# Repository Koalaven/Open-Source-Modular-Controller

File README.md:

# Open Source Modular Controller

Using a modular, reconfigurable hardware architecture to create a customizable USB HID game controller.

## Project Details

The Open Source Modular Controller project is a fully modular and customizable gaming input system. Users can freely rearrange joysticks, buttons, and future input modules on a set of interchangeable receiver boards to build a layout that fits their gameplay style, ergonomic needs, or accessibility requirements.

The controller connects over USB and is recognized as a standard Human Interface Device (HID) with no additional drivers required.

## Current State

The current prototype includes:
- A functional ESP32‑S3‑based main controller
- Hot-swappable joystick and button modules
- Receiver boards that can be placed anywhere in the 3D‑printed shell
- USB HID communication via TinyUSB

The system operates as a recognized USB gamepad on Windows. Some hardware issues were identified and corrected in updated revisions.

## Project Structure

The repository is organized as follows:
1. **Firmware** – ESP32‑S3 code handling HID communication and module input processing.  
   *Link: [Firmware](/Controller%20Code/Firmware.md)*
2. **Software** – PC‑side utilities or test scripts (coming soon).  
3. **Hardware** – KiCad project files, schematics, PCBs, and 3D‑printed shell models.  
   *Link: [Hardware](/Hardware/Hardware.md)*
4. **Documentation** – Assembly instructions, diagrams, semester report, and testing notes.  
   *Link: [Documentation](/Documents/Documents.md)*

## Features

- Modular input modules (buttons, joystick, future sensors)
- Repositionable input layout using multiple receiver boards
- ESP32‑S3 native USB HID support
- Open‑source hardware and firmware
- Premade 3D‑printable ergonomic controller shell

## System Architecture

Core system components include:
- **Receiver boards** distributing power, signals, and micro-controller
- **Module boards** for inputs (joystick/button)
- **3D‑printed enclosure** with heat‑set inserts for secure mounting

USB HID enumeration and report handling are implemented using TinyUSB. Modules communicate through standardized connectors to the controller board.

## Bill of Materials
A full BOM including the ESP32‑S3 boards, connector sets, resistors, capacitors, PCBs, wire, and 3D‑printed components is provided in the documentation.  
*[BOM](/Documents/BOM.md)*

## Tools Used
### Software
- Arduino IDE
- KiCad
- Fusion (frame design)
- GitHub Desktop
- Cura slicer

### Hardware
- 3D printer
- Soldering iron
- Hot air station
- Multimeter
- Tweezers

## Assembly Overview
1. Gather materials (refer to BOM).  
2. Order PCBs (Gerber files included).  
3. 3D print shell and module housings.  
4. Clean and prepare boards.  
5. Solder components (headers, ESP32 module, connectors, buttons/joysticks).  
6. Upload firmware via Arduino IDE.  
7. Install modules into the shell.  
8. Test controller.  

[Full assembly guide](/Documents/Assembly%20guide.md)

## What the Project Could Use Next
1. On‑board processing for more advanced input mapping
2. PCB adjustment and testing
3. Wireless mode using Bluetooth HID
4. Additional module types (battery, gyroscope, sliders, touchpads)

## Semester End Report
For the Enterprise Program at Michigan Tech there is a end of semester report for the project to summarize the progress of the project. [Link](/Documents/Open%20Source%20Modular%20Controller%20Fall%202025%20Final%20Report.pdf)

## Acknowledgements
This project is supported by the Open Source Hardware Enterprise at Michigan Technological University.

## Helpful Links
- [TinyUSB](https://docs.tinyusb.org/en/latest/)
- [Gamepad tester](https://hardwaretester.com/gamepad)

## References

[GitHub Doc](https://docs.github.com/en/get-started/writing-on-github/getting-started-with-writing-and-formatting-on-github/basic-writing-and-formatting-syntax#links)

[Alpakka conroller](https://inputlabs.io/alpakka)

[Proteus ControllerTM kit](https://byowave.com/products/proteus-controller )

[Thrustmaster](https://eshop.thrustmaster.com/en_us/gamepads/pc.html)

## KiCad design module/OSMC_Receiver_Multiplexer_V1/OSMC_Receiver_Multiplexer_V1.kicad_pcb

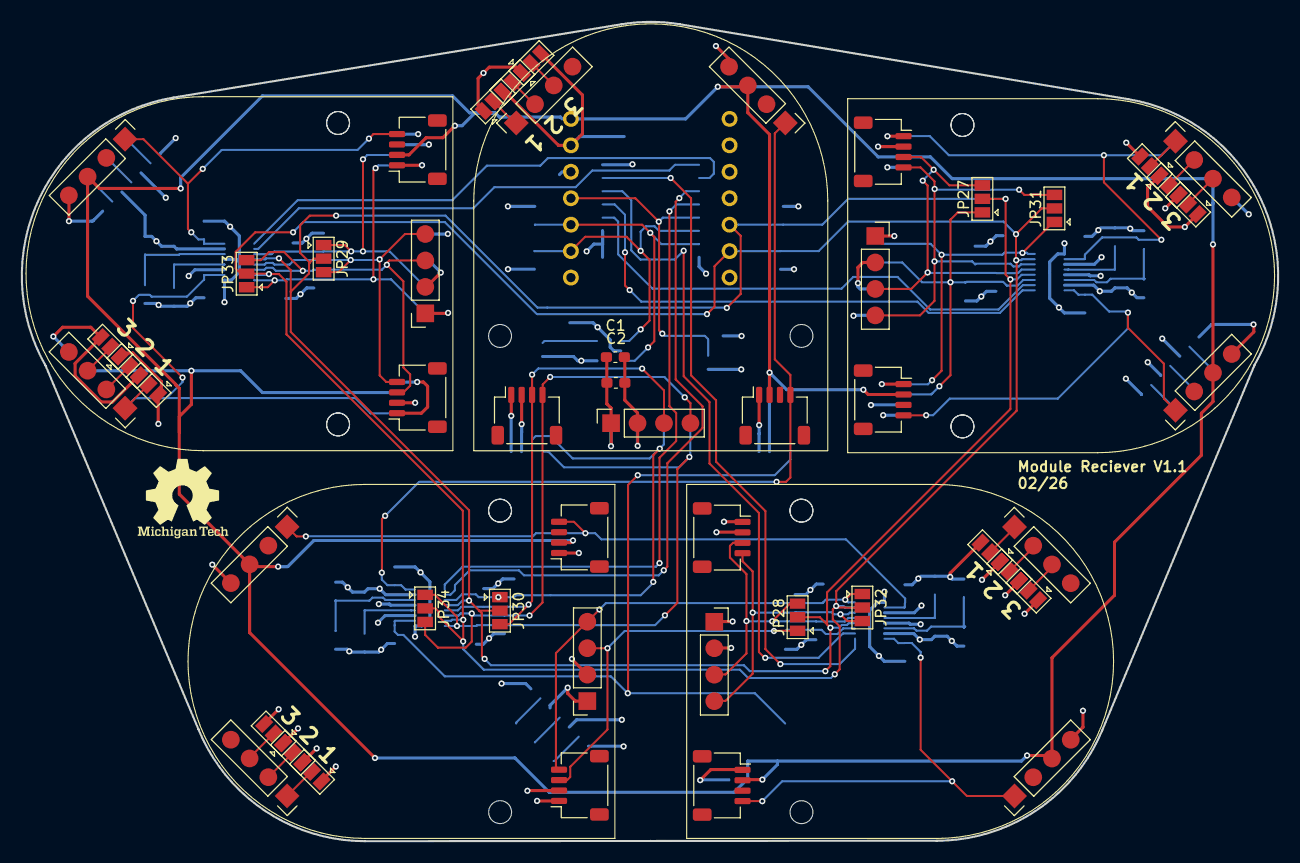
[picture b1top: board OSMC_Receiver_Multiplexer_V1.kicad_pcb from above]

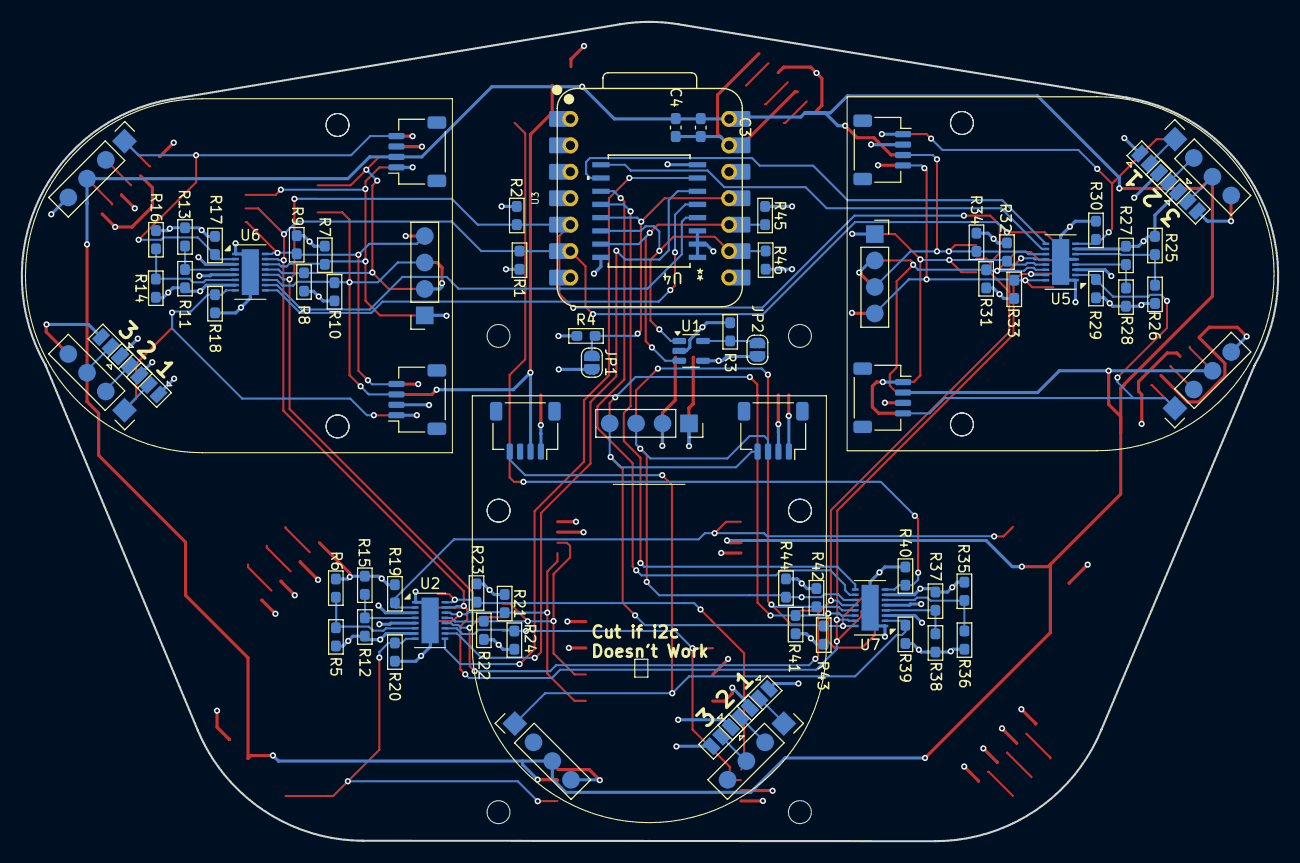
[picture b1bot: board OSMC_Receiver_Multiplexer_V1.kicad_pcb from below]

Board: 4 copper layers, 120.7 x 78.7 mm, 99 parts (69 on the bottom side), 73 nets.

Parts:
C1, C2: .1 u; C_0603_1608Metric_Pad1.08x0.95mm_HandSolder
C3, C4: C; C_0603_1608Metric_Pad1.08x0.95mm_HandSolder
JP1: int; SolderJumper-2_P1.3mm_Open_RoundedPad1.0x1.5mm
JP2: WP; SolderJumper-2_P1.3mm_Open_RoundedPad1.0x1.5mm
JP3, JP4, JP5, JP6, JP7, JP8, JP9, JP10, JP11, JP12, JP13, JP14, JP15, JP16, JP17, JP18, JP19, JP20, JP21, JP22, JP23, JP24, JP25, JP26, JP27, JP28, JP29, JP30, JP31, JP32, JP33, JP34: SolderJumper_3_Open; SolderJumper-3_P1.3mm_Open_Pad1.0x1.5mm
R1, R2, R7, R8, R9, R10, R17, R18, R19, R20, R21, R22, R23, R24, R29, R30, R31, R32, R33, R34, R39, R40, R41, R42, R43, R44, R45, R46: 10k; R_0603_1608Metric_Pad1.05x0.95mm_HandSolder
R3, R4: 100k; R_0603_1608Metric_Pad1.05x0.95mm_HandSolder
R5, R11: 976k; R_0603_1608Metric_Pad1.05x0.95mm_HandSolder
R6: 182k; R_0603_1608Metric_Pad1.05x0.95mm_HandSolder
R12: 1M; R_0603_1608Metric_Pad1.05x0.95mm_HandSolder
R13: 102k; R_0603_1608Metric_Pad1.05x0.95mm_HandSolder
R14: R; R_0603_1608Metric_Pad1.05x0.95mm_HandSolder
R15: 280k; R_0603_1608Metric_Pad1.05x0.95mm_HandSolder
R16: 0; R_0603_1608Metric_Pad1.05x0.95mm_HandSolder
R25, R27, R35, R37: 1000k; R_0603_1608Metric_Pad1.05x0.95mm_HandSolder
R26: 392k; R_0603_1608Metric_Pad1.05x0.95mm_HandSolder
R28: 523k; R_0603_1608Metric_Pad1.05x0.95mm_HandSolder
R36: 681k; R_0603_1608Metric_Pad1.05x0.95mm_HandSolder
R38: 887k; R_0603_1608Metric_Pad1.05x0.95mm_HandSolder
U1: 24AA02-OT; SOT-23-5
U2, U5, U6, U7: LTC4317; DFN-16-1EP_3x5mm_P0.5mm_EP1.66x4.4mm
U3: XIAO-ESP32-S3-DIP
U4: PCF8574DWR; DW16-L
U13, U14, U15, U16, U17, U18, U19, U20: OSMC Module Board; Module standard pin large outline

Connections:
+5V: C3.1, C4.1, U3.14 (5V), U13.10 (5V), U13.15 (5V), U14.10 (5V), U14.15 (5V), U15.10 (5V), U15.15 (5V), U16.10 (5V), U16.15 (5V), U17.10 (5V), U17.15 (5V), U18.10 (5V), U18.15 (5V), U19.10 (5V), U19.15 (5V), U20.10 (5V), U20.15 (5V)
/INT: JP1.1 (A), R4.2, U3.11 (PA6_A10_D10_MOSI), U4.13 (~INT)
/Modules/EN0: R18.2, U6.8 (ENABLE1), U13.12 (Det), U13.13 (Det)
/Modules/EN1: R17.2, U6.2 (ENABLE2), U15.12 (Det), U15.13 (Det)
/Modules/EN2: R20.2, U2.8 (ENABLE1), U16.12 (Det), U16.13 (Det)
/Modules/EN3: R19.2, U2.2 (ENABLE2), U18.12 (Det), U18.13 (Det)
/Modules/EN4: R30.2, U5.8 (ENABLE1), U17.12 (Det), U17.13 (Det)
/Modules/EN5: R29.2, U5.2 (ENABLE2), U20.12 (Det), U20.13 (Det)
/Modules/EN6: R40.2, U7.8 (ENABLE1), U14.12 (Det), U14.13 (Det)
/Modules/EN7: R39.2, U7.2 (ENABLE2), U19.12 (Det), U19.13 (Det)
/Modules/P0: U4.4 (P0), U6.10 (READY1)
/Modules/P1: U4.5 (P1), U6.9 (READY2)
/Modules/P2: U2.10 (READY1), U4.6 (P2)
/Modules/P3: U2.9 (READY2), U4.7 (P3)
/Modules/P4: U4.9 (P4), U5.10 (READY1)
/Modules/P5: U4.10 (P5), U5.9 (READY2)
/Modules/P6: U4.11 (P6), U7.10 (READY1)
/Modules/P7: U4.12 (P7), U7.9 (READY2)
/Modules/SCL0: JP31.3 (B), R7.2, U6.14 (SCLOUT1), U13.4 (SCL), U13.8 (SCL)
/Modules/SCL1: JP31.1 (A), R9.2, U6.16 (SCLOUT2), U15.4 (SCL), U15.8 (SCL)
/Modules/SCL2: JP32.3 (B), R21.2, U2.14 (SCLOUT1), U16.4 (SCL), U16.8 (SCL)
/Modules/SCL3: JP32.1 (A), R23.2, U2.16 (SCLOUT2), U18.4 (SCL), U18.8 (SCL)
/Modules/SCL4: JP33.3 (B), R31.2, U5.14 (SCLOUT1), U17.3 (SDA), U17.7 (SDA)
/Modules/SCL5: JP33.1 (A), R33.2, U5.16 (SCLOUT2), U20.4 (SCL), U20.8 (SCL)
/Modules/SCL6: JP34.3 (B), R41.2, U7.14 (SCLOUT1), U14.4 (SCL), U14.8 (SCL)
/Modules/SCL7: JP34.1 (A), R43.2, U7.16 (SCLOUT2), U19.4 (SCL), U19.8 (SCL)
/Modules/SDA0: JP27.3 (B), R8.2, U6.13 (SDAOUT1), U13.3 (SDA), U13.7 (SDA)
/Modules/SDA1: JP27.1 (A), R10.2, U6.11 (SDAOUT2), U15.3 (SDA), U15.7 (SDA)
/Modules/SDA2: JP28.3 (B), R22.2, U2.13 (SDAOUT1), U16.3 (SDA), U16.7 (SDA)
/Modules/SDA3: JP28.1 (A), R24.2, U2.11 (SDAOUT2), U18.3 (SDA), U18.7 (SDA)
/Modules/SDA4: JP29.3 (B), R32.2, U5.13 (SDAOUT1), U17.4 (SCL), U17.8 (SCL)
/Modules/SDA5: JP29.1 (A), R34.2, U5.11 (SDAOUT2), U20.3 (SDA), U20.7 (SDA)
/Modules/SDA6: JP30.3 (B), R42.2, U7.13 (SDAOUT1), U14.3 (SDA), U14.7 (SDA)
/Modules/SDA7: JP30.1 (A), R44.2, U7.11 (SDAOUT2), U19.3 (SDA), U19.7 (SDA)
/SCL: JP31.2 (C), JP32.2 (C), JP33.2 (C), JP34.2 (C), R1.2, U2.15 (SCLIN), U3.6 (PA9_A5_D5_SCL), U5.15 (SCLIN), U6.15 (SCLIN), U7.15 (SCLIN)
/SCL1: R46.2, U1.1 (SCL), U3.9 (PA7_A8_D8_SCK), U4.14 (SCL)
/SDA: JP27.2 (C), JP28.2 (C), JP29.2 (C), JP30.2 (C), R2.2, U2.12 (SDAIN), U3.5 (PA8_A4_D4_SDA), U5.12 (SDAIN), U6.12 (SDAIN), U7.12 (SDAIN)
/SDA1: R45.2, U1.3 (SDA), U3.10 (PA5_A9_D9_MISO), U4.15 (SDA)
/wp: JP2.1 (A), R3.2, U1.5 (WP)
GND: C1.2, C2.2, C3.2, C4.2, JP3.3 (B), JP4.3 (B), JP5.3 (B), JP6.3 (B), JP7.3 (B), JP8.3 (B), JP9.3 (B), JP10.3 (B), JP11.3 (B), JP12.3 (B), JP13.3 (B), JP14.3 (B), JP15.3 (B), JP16.3 (B), JP17.3 (B), JP18.3 (B), JP19.3 (B), JP20.3 (B), JP21.3 (B), JP22.3 (B), JP23.3 (B), JP24.3 (B), JP25.3 (B), JP26.3 (B), R3.1, R4.1, R6.2, R13.2, R15.2, R16.2, R17.1, R18.1, R19.1, R20.1, R26.2, R28.2, R29.1, R30.1, R36.2, R38.2, R39.1, R40.1, U1.2 (V_{SS}), U2.1 (GND), U2.3 (XORH2), U2.5 (XORH1), U2.17 (EP), U3.13 (GND), U4.1 (A0), U4.2 (A1), U4.3 (A2), U4.8 (GND), U5.1 (GND), U5.3 (XORH2), U5.5 (XORH1), U5.17 (EP), U6.1 (GND), U6.3 (XORH2), U6.5 (XORH1), U6.17 (EP), U7.1 (GND), U7.3 (XORH2), U7.5 (XORH1), U7.17 (EP), U13.1 (Gnd), U13.5 (Gnd), U13.9 (Gnd), U13.16 (GND), U14.1 (Gnd), U14.5 (Gnd), U14.9 (Gnd), U14.16 (GND), U15.1 (Gnd), U15.5 (Gnd), U15.9 (Gnd), U15.16 (GND), U16.1 (Gnd), U16.5 (Gnd), U16.9 (Gnd), U16.16 (GND), U17.1 (Gnd), U17.5 (Gnd), U17.9 (Gnd), U17.16 (GND), U18.1 (Gnd), U18.5 (Gnd), U18.9 (Gnd), U18.16 (GND), U19.1 (Gnd), U19.5 (Gnd), U19.9 (Gnd), U19.16 (GND), U20.1 (Gnd), U20.5 (Gnd), U20.9 (Gnd), U20.16 (GND)
unnamed: JP3.2 (C), U16.18 (A3)
unnamed: JP4.2 (C), U16.19 (A2)
unnamed: JP5.2 (C), U16.20 (A1)
unnamed: JP6.2 (C), U15.18 (A3)
unnamed: JP7.2 (C), U15.19 (A2)
unnamed: JP8.2 (C), U15.20 (A1)
unnamed: JP9.2 (C), U13.18 (A3)
unnamed: JP10.2 (C), U13.19 (A2)
unnamed: JP11.2 (C), U13.20 (A1)
unnamed: JP12.2 (C), U18.18 (A3)
unnamed: JP13.2 (C), U18.19 (A2)
unnamed: JP14.2 (C), U18.20 (A1)
unnamed: JP15.2 (C), U19.18 (A3)
unnamed: JP16.2 (C), U19.19 (A2)
unnamed: JP17.2 (C), U19.20 (A1)
unnamed: JP18.2 (C), U17.18 (A3)
unnamed: JP19.2 (C), U17.19 (A2)
unnamed: JP20.2 (C), U17.20 (A1)
unnamed: JP21.2 (C), U20.18 (A3)
unnamed: JP22.2 (C), U20.19 (A2)
unnamed: JP23.2 (C), U20.20 (A1)
unnamed: JP24.2 (C), U14.18 (A3)
unnamed: JP25.2 (C), U14.19 (A2)
unnamed: JP26.2 (C), U14.20 (A1)
unnamed: R5.2, R6.1, U2.6 (XORL1)
unnamed: R12.2, R15.1, U2.4 (XORL2)
unnamed: R25.2, R26.1, U5.6 (XORL1)
unnamed: R27.2, R28.1, U5.4 (XORL2)
unnamed: R14.2, R16.1, U6.6 (XORL1)
unnamed: R11.2, R13.1, U6.4 (XORL2)
unnamed: R35.2, R36.1, U7.6 (XORL1)
unnamed: R37.2, R38.1, U7.4 (XORL2)
VDD: C1.1, C2.1, JP1.2 (B), JP2.2 (B), JP3.1 (A), JP4.1 (A), JP5.1 (A), JP6.1 (A), JP7.1 (A), JP8.1 (A), JP9.1 (A), JP10.1 (A), JP11.1 (A), JP12.1 (A), JP13.1 (A), JP14.1 (A), JP15.1 (A), JP16.1 (A), JP17.1 (A), JP18.1 (A), JP19.1 (A), JP20.1 (A), JP21.1 (A), JP22.1 (A), JP23.1 (A), JP24.1 (A), JP25.1 (A), JP26.1 (A), R1.1, R2.1, R5.1, R7.1, R8.1, R9.1, R10.1, R11.1, R12.1, R14.1, R21.1, R22.1, R23.1, R24.1, R25.1, R27.1, R31.1, R32.1, R33.1, R34.1, R35.1, R37.1, R41.1, R42.1, R43.1, R44.1, R45.1, R46.1, U1.4 (V_{CC}), U2.7 (VCC), U3.12 (3V3), U4.16 (VDD), U5.7 (VCC), U6.7 (VCC), U7.7 (VCC), U13.2 (Vdd), U13.6 (Vdd), U14.2 (Vdd), U14.6 (Vdd), U15.2 (Vdd), U15.6 (Vdd), U16.2 (Vdd), U16.6 (Vdd), U17.2 (Vdd), U17.6 (Vdd), U18.2 (Vdd), U18.6 (Vdd), U19.2 (Vdd), U19.6 (Vdd), U20.2 (Vdd), U20.6 (Vdd)

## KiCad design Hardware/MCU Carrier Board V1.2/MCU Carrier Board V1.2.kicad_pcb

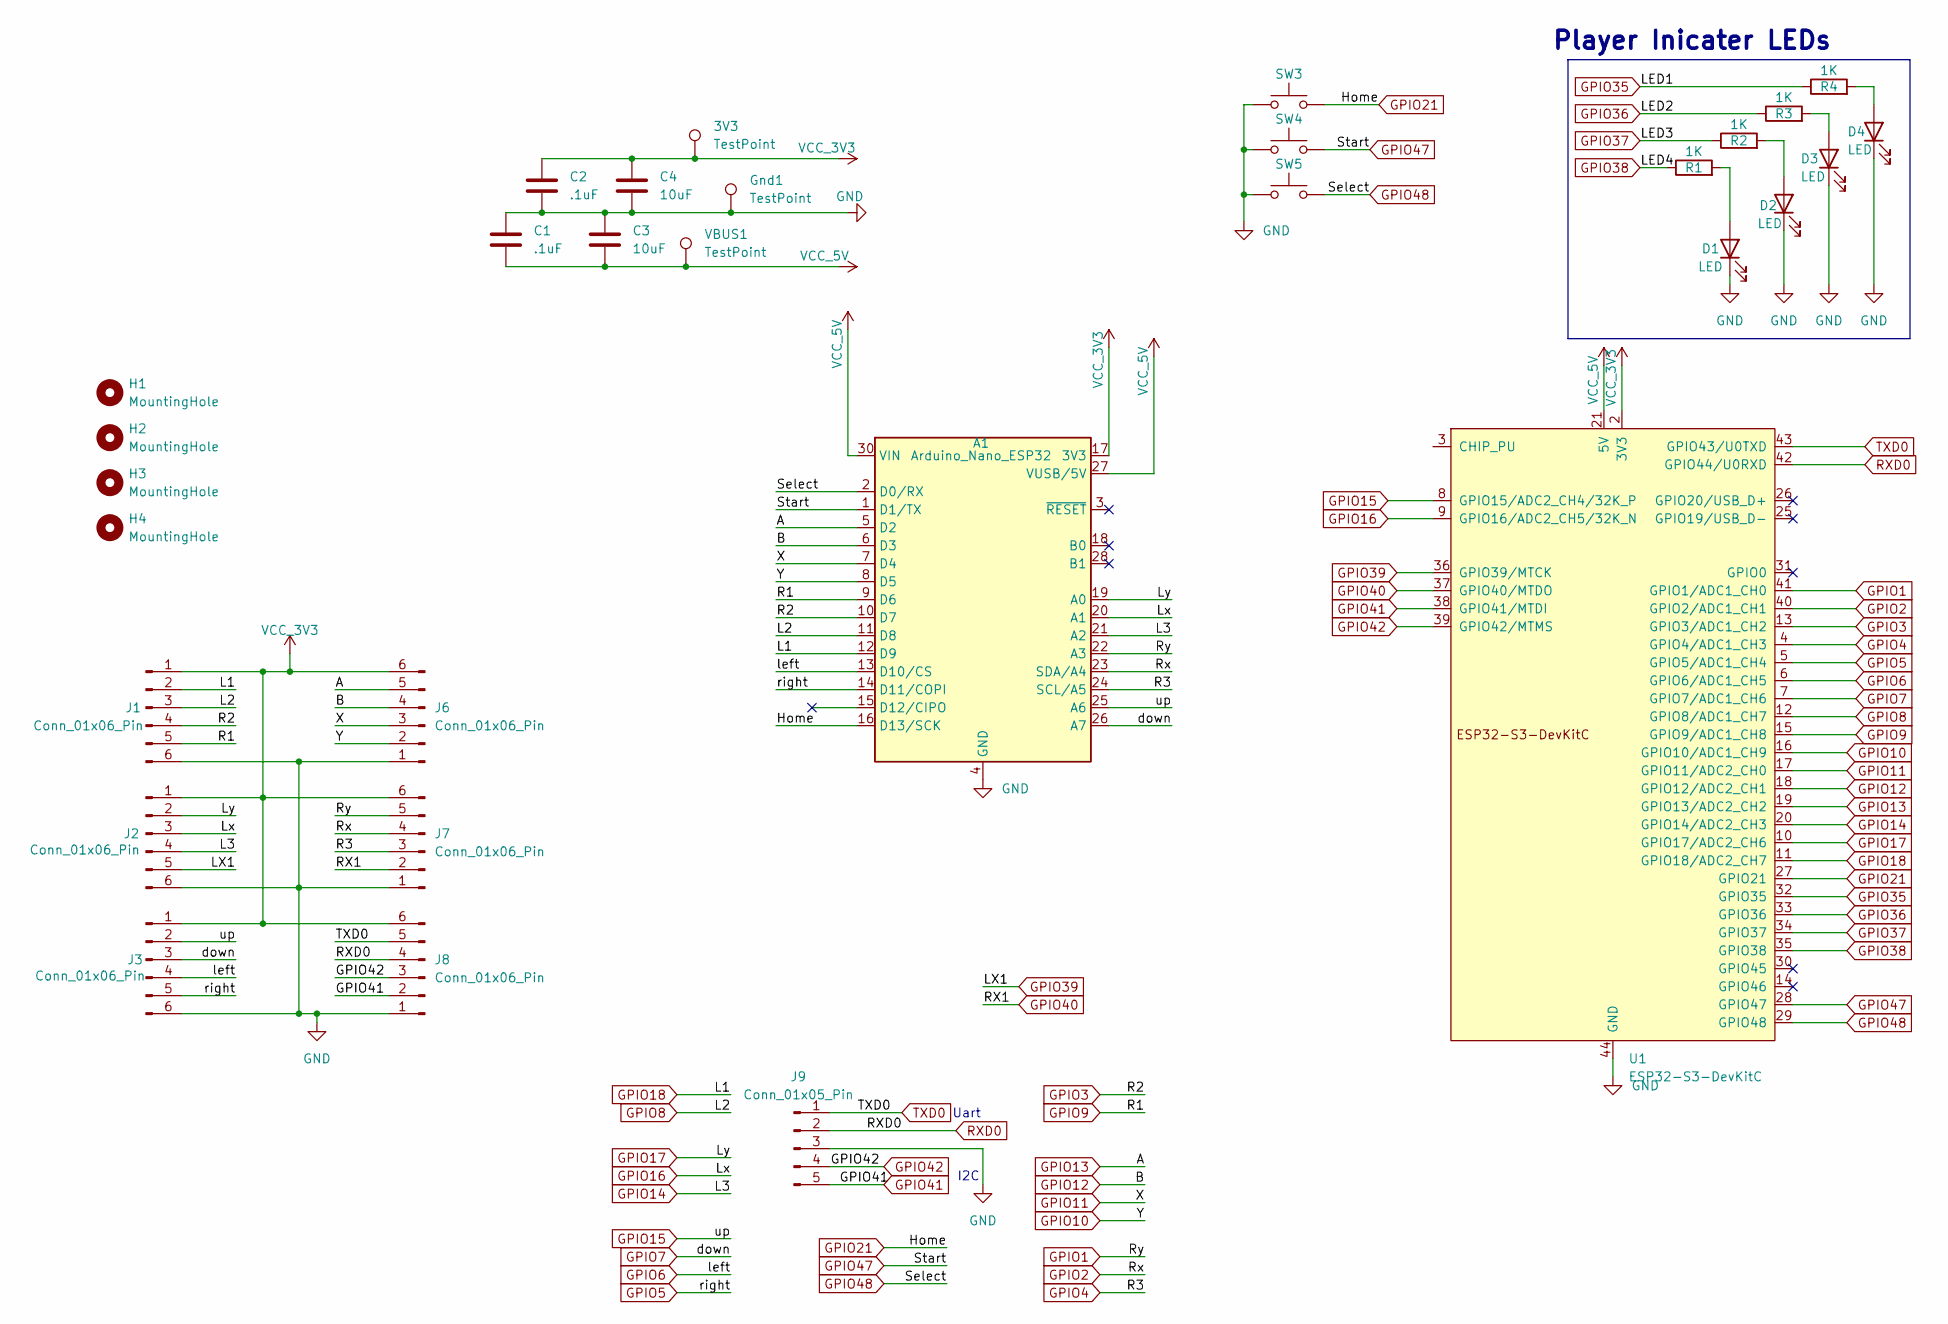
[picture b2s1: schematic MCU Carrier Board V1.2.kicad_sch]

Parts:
3V3: TestPoint; TestPoint_Pad_D1.0mm
A1: Arduino_Nano_ESP32; Arduino_Nano_WithMountingHoles
C1, C2: .1uF; C_0603_1608Metric_Pad1.08x0.95mm_HandSolder
C3, C4: 10uF; C_0603_1608Metric_Pad1.08x0.95mm_HandSolder
D1, D2, D3, D4: LED; LED_0603_1608Metric_Pad1.05x0.95mm_HandSolder
Gnd1: TestPoint; TestPoint_Pad_D1.0mm
H1, H2, H3, H4: MountingHole; MountingHole_2.5mm
J1, J2, J3, J6, J7, J8: Conn_01x06_Pin; PinHeader_1x06_P2.54mm_Vertical
J9: Conn_01x05_Pin; JST_EH_S5B-EH_1x05_P2.50mm_Horizontal
R1, R2, R3, R4: 1K; R_0603_1608Metric_Pad0.98x0.95mm_HandSolder
SW3, SW4, SW5: SW_Push; SW_Push_1P1T_XKB_TS-1187A
U1: ESP32-S3-DevKitC
VBUS1: TestPoint; TestPoint_Pad_D1.0mm

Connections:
GND: A1.4 (GND), A1.29 (GND), C1.1, C2.2, C3.1, C4.2, D1.1 (K), D2.1 (K), D3.1 (K), D4.1 (K), Gnd1.1, J1.6, J2.6, J3.6, J6.1, J7.1, J8.1, J9.3, SW3.1, SW4.1, SW5.1, U1.22 (GND), U1.23 (GND), U1.24 (GND), U1.44 (GND)
GPIO1: A1.22 (A3), J7.5, U1.41 (GPIO1/ADC1_CH0)
GPIO2: A1.23 (SDA/A4), J7.4, U1.40 (GPIO2/ADC1_CH1)
GPIO3: A1.10 (D7), J1.4, U1.13 (GPIO3/ADC1_CH2)
GPIO4: A1.24 (SCL/A5), J7.3, U1.4 (GPIO4/ADC1_CH3)
GPIO5: A1.14 (D11/COPI), J3.5, U1.5 (GPIO5/ADC1_CH4)
GPIO6: A1.13 (D10/CS), J3.4, U1.6 (GPIO6/ADC1_CH5)
GPIO7: A1.26 (A7), J3.3, U1.7 (GPIO7/ADC1_CH6)
GPIO8: A1.11 (D8), J1.3, U1.12 (GPIO8/ADC1_CH7)
GPIO9: A1.9 (D6), J1.5, U1.15 (GPIO9/ADC1_CH8)
GPIO10: A1.8 (D5), J6.2, U1.16 (GPIO10/ADC1_CH9)
GPIO11: A1.7 (D4), J6.3, U1.17 (GPIO11/ADC2_CH0)
GPIO12: A1.6 (D3), J6.4, U1.18 (GPIO12/ADC2_CH1)
GPIO13: A1.5 (D2), J6.5, U1.19 (GPIO13/ADC2_CH2)
GPIO14: A1.21 (A2), J2.4, U1.20 (GPIO14/ADC2_CH3)
GPIO15: A1.25 (A6), J3.2, U1.8 (GPIO15/ADC2_CH4/32K_P)
GPIO16: A1.20 (A1), J2.3, U1.9 (GPIO16/ADC2_CH5/32K_N)
GPIO17: A1.19 (A0), J2.2, U1.10 (GPIO17/ADC2_CH6)
GPIO18: A1.12 (D9), J1.2, U1.11 (GPIO18/ADC2_CH7)
GPIO21: A1.16 (D13/SCK), SW3.2, U1.27 (GPIO21)
GPIO35: R4.1, U1.32 (GPIO35)
GPIO36: R3.1, U1.33 (GPIO36)
GPIO37: R2.1, U1.34 (GPIO37)
GPIO38: R1.1, U1.35 (GPIO38)
GPIO39: J2.5, U1.36 (GPIO39/MTCK)
GPIO40: J7.2, U1.37 (GPIO40/MTDO)
GPIO41: J8.2, J9.5, U1.38 (GPIO41/MTDI)
GPIO42: J8.3, J9.4, U1.39 (GPIO42/MTMS)
GPIO47: A1.1 (D1/TX), SW4.2, U1.28 (GPIO47)
GPIO48: A1.2 (D0/RX), SW5.2, U1.29 (GPIO48)
unnamed: D1.2 (A), R1.2
unnamed: D2.2 (A), R2.2
unnamed: D3.2 (A), R3.2
unnamed: D4.2 (A), R4.2
RXD0: J8.4, J9.2, U1.42 (GPIO44/U0RXD)
TXD0: J8.5, J9.1, U1.43 (GPIO43/U0TXD)
VCC_3V3: 3V3.1, A1.17 (3V3), C2.1, C4.1, J1.1, J2.1, J3.1, J6.6, J7.6, J8.6, U1.1 (3V3), U1.2 (3V3)
VCC_5V: A1.27 (VUSB/5V), A1.30 (VIN), C1.2, C3.2, U1.21 (5V), VBUS1.1

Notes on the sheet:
Player Inicater LEDs
Uart
I2C

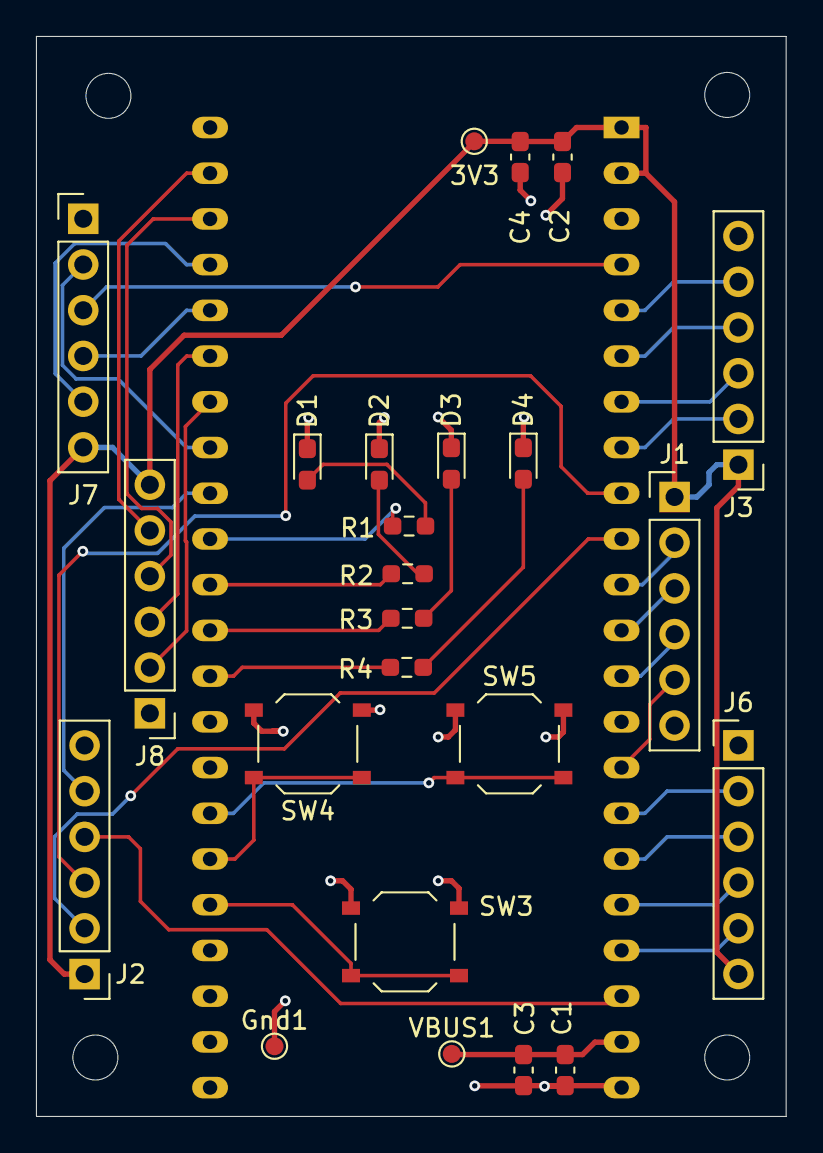
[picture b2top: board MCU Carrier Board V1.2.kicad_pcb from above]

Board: 2 copper layers, 41.7 x 60.0 mm, 29 parts (1 on the bottom side), 38 nets.

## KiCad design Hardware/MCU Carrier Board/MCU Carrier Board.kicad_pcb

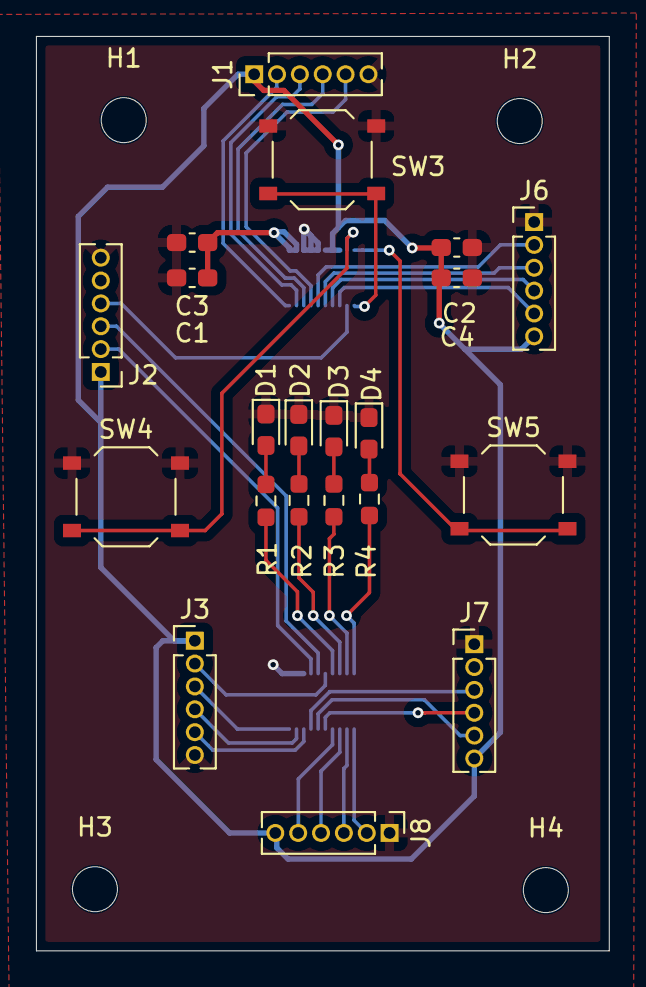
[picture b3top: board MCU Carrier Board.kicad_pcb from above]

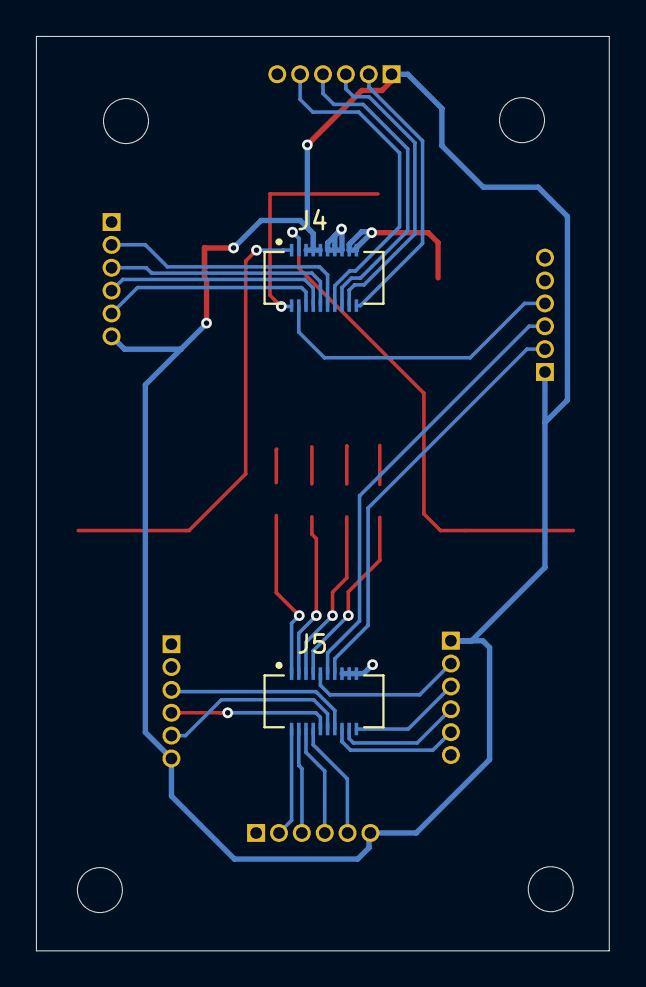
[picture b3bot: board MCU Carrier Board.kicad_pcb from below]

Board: 2 copper layers, 31.8 x 50.8 mm, 27 parts (2 on the bottom side), 36 nets.

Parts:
C1, C2: .1uF; C_0603_1608Metric_Pad1.08x0.95mm_HandSolder
C3, C4: 10uF; C_0603_1608Metric_Pad1.08x0.95mm_HandSolder
D1, D2, D3, D4: LED; LED_0603_1608Metric_Pad1.05x0.95mm_HandSolder
H1, H2, H3, H4: MountingHole; MountingHole_2.5mm
J1, J2, J3, J6, J7, J8: Conn_01x06_Pin; PinHeader_1x06_P1.27mm_Vertical
J4: Top Connector; HRS_DF40C-20DS-0.4V_51_
J5: Bottom Connector; HRS_DF40C-20DS-0.4V_51_
R1, R2, R3, R4: 1K; R_0603_1608Metric_Pad0.98x0.95mm_HandSolder
SW3, SW4, SW5: SW_Push; SW_Push_1P1T_XKB_TS-1187A

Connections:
GND: C1.1, C2.2, C3.1, C4.2, D1.1 (K), D2.1 (K), D3.1 (K), D4.1 (K), J1.6, J2.6, J3.6, J4.11, J4.13, J4.15, J5.15, J5.17, J5.19, J6.1, J7.1, J8.1, SW3.1, SW4.1, SW5.1
GPIO1: J5.12, J7.5
GPIO2: J5.10, J7.4
GPIO3: J1.4, J4.16
GPIO4: J5.14, J7.3
GPIO5: J3.5, J5.16
GPIO6: J3.4, J5.18
GPIO7: J3.3, J5.20
GPIO8: J1.3, J4.18
GPIO9: J1.5, J4.14
GPIO10: J4.12, J6.2
GPIO11: J4.10, J6.3
GPIO12: J4.8, J6.4
GPIO13: J4.6, J6.5
GPIO14: J2.4, J4.4
GPIO15: J3.2, J5.9
GPIO16: J2.3, J5.11
GPIO17: J2.2, J5.13
GPIO18: J1.2, J4.20
GPIO21: J4.2, SW3.2
GPIO35: J5.1, R4.1
GPIO36: J5.3, R3.1
GPIO37: J5.5, R2.1
GPIO38: J5.7, R1.1
GPIO41: J5.2, J8.2
GPIO42: J5.4, J8.3
GPIO47: J4.3, SW4.2
GPIO48: J4.1, SW5.2
unnamed: D1.2 (A), R1.2
unnamed: D2.2 (A), R2.2
unnamed: D3.2 (A), R3.2
unnamed: D4.2 (A), R4.2
RXD0: J5.6, J8.4
TXD0: J5.8, J8.5
VCC_3V3: C2.1, C4.1, J1.1, J2.1, J3.1, J4.5, J4.7, J4.9, J6.6, J7.6, J8.6
VCC_5V: C1.2, C3.2, J4.17, J4.19

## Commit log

2025-09-18 test
2025-09-19 added ESP-IDF code files
2025-09-26 starting board
2025-09-26 added outline
2025-09-26 start
2025-09-30 locked placement of key components
2025-09-30 reconfigured pins and started routing
2025-09-30 Added design rule made v.1 of board
2025-10-02 new test
2025-10-03 remove build files
2025-10-07 edit
2025-10-07 added new code of esp-idf
2025-10-08 test hid config files
2025-10-08 updated testcode
2025-10-08 small update
2025-10-09 files to look through
2025-10-09 fixed error in test cases
2025-10-13 changed library used
    change to the esp32 implementation of tinyusb
2025-10-27 Arduino ide config
2025-10-27 for dev board carrier
2025-11-10 update code
2025-11-11 Add files via upload
    CAD go brrrrrrrrrrrrrrrrrr
2025-11-15 Add files via upload
    on board configuration
2026-03-12 new chip emulation code
2026-04-20 PCB version update
2026-04-22 Update README.md
    small changes
    replaced Onshape with Fusion under software
    added premade to the case for features
2026-04-22 Delete Hardware/Shell/OSMC_Shell2.stl
    removed way out of date model that I created
2026-04-22 Update Assembly guide.md
    Updated the Shell printing and assembly instructions
